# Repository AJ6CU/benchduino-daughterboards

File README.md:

# CPU Daughterboards Benchduino
 
www.hamradioworkbench.com has designed and sells a general purpose development
board for Microcontrollers. They have provided the designs for both the CPU
Daughterboards as wells as the addon Prototype board.

This repository contains additional CPU Daughterboards that I have designed.

Subdirectories include:
- Gerbers - this directory includes a zip file that you should be able to upload to
            your favorite Fab house.
- PCBDesign - Most of the designs are done with KiCad. A few of the earlier ones
            were done with Eagle. The subdirectory will indentify which tool was used. 
- Documentation - This directory contains a schematic (pdf format) and pinmapping between
            the Benchduino pins and the pins on the Microcontroller. Please note that
            some physical pins on the Microcontroller might be mapped to multiple 
            locations on the Benchduino. Please use this pinmapping document along
            with your favorite pinout diagram to understand which pins could cause
            conflicts.
- Examples - Generally I have provide a code example (typically derived from the
            original Hamvention code of the published on the hamradioworkbench site)

There is absolutely no warranty here. Use this at your own risk!

73
Mark Hatch
AJ6CU

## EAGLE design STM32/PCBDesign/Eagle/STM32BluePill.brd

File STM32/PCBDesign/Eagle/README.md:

# Eagle files for the STM32 "BluePill" Series MCU Daughterboard

This directory includes the Eagle files for a design of a Benchduino Daughterboard
(see https://www.hamradioworkbench.com ) for the STM32 "BluePill" series of MCU.

This folder includes:
- STM32BluePill.sch - schematic
- STM32BluePill.brd - board layout

It is possible that you will need the Eagle library for STM32. I found it with a little
googling.

In making this design, my philosophy was to try to make sure most Benchduino Pins were 
connected to appropriate pins if possible.

This means that some pins (e.g. SDA, and A4) are both active and map to the same pin 
on the STM32. So don't assume that because you have two pins, that they are separate. 
The STM32 pin guide is your friend to make sure you don't use the same pin twice
for a different purpose.

Feedback is appreciated!

73
Mark
AJ6CU

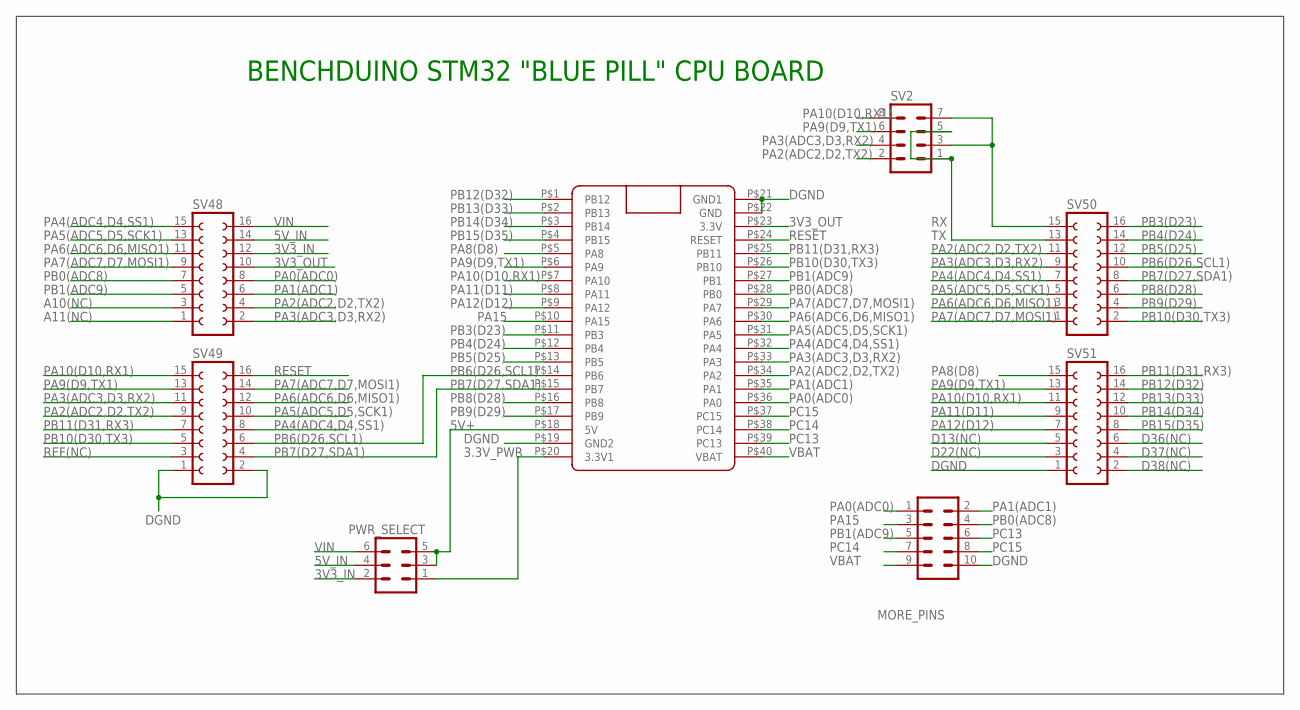
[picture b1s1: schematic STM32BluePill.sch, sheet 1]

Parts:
MORE_PINS: MA05-2
PWR_SELECT: MA03-2
SV2: MA04-2
SV48, SV49, SV50, SV51: FE08-2
U$1: BLUE_PILLADVANCED; BLUE_PILL_ADV

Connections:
3.3V_PWR: PWR_SELECT.1, U$1.P$20 (3.3V1)
3V3_IN: PWR_SELECT.2, SV48.12
3V3_OUT: SV48.10, U$1.P$23 (3.3V)
5V+: PWR_SELECT.3, PWR_SELECT.5, U$1.P$18 (5V)
5V_IN: PWR_SELECT.4, SV48.14
A10(NC): SV48.3
A11(NC): SV48.1
D13(NC): SV51.5
D22(NC): SV51.3
D36(NC): SV51.6
D37(NC): SV51.4
D38(NC): SV51.2
DGND: MORE_PINS.10, SV49.1, SV49.2, SV51.1, U$1.P$19 (GND2), U$1.P$21 (GND1), U$1.P$22 (GND)
PA0(ADC0): MORE_PINS.1, SV48.8, U$1.P$36 (PA0)
PA1(ADC1): MORE_PINS.2, SV48.6, U$1.P$35 (PA1)
PA2(ADC2,D2,TX2): SV2.2, SV48.4, SV49.9, SV50.11, U$1.P$34 (PA2)
PA3(ADC3,D3,RX2): SV2.4, SV48.2, SV49.11, SV50.9, U$1.P$33 (PA3)
PA4(ADC4,D4,SS1): SV48.15, SV49.8, SV50.7, U$1.P$32 (PA4)
PA5(ADC5,D5,SCK1): SV48.13, SV49.10, SV50.5, U$1.P$31 (PA5)
PA6(ADC6,D6,MISO1): SV48.11, SV49.12, SV50.3, U$1.P$30 (PA6)
PA7(ADC7,D7,MOSI1): SV48.9, SV49.14, SV50.1, U$1.P$29 (PA7)
PA8(D8): SV51.15, U$1.P$5 (PA8)
PA9(D9,TX1): SV2.6, SV49.13, SV51.13, U$1.P$6 (PA9)
PA10(D10,RX1): SV2.8, SV49.15, SV51.11, U$1.P$7 (PA10)
PA11(D11): SV51.9, U$1.P$8 (PA11)
PA12(D12): SV51.7, U$1.P$9 (PA12)
PA15: MORE_PINS.3, U$1.P$10 (PA15)
PB0(ADC8): MORE_PINS.4, SV48.7, U$1.P$28 (PB0)
PB1(ADC9): MORE_PINS.5, SV48.5, U$1.P$27 (PB1)
PB3(D23): SV50.16, U$1.P$11 (PB3)
PB4(D24): SV50.14, U$1.P$12 (PB4)
PB5(D25): SV50.12, U$1.P$13 (PB5)
PB6(D26,SCL1): SV49.6, SV50.10, U$1.P$14 (PB6)
PB7(D27,SDA1): SV49.4, SV50.8, U$1.P$15 (PB7)
PB8(D28): SV50.6, U$1.P$16 (PB8)
PB9(D29): SV50.4, U$1.P$17 (PB9)
PB10(D30,TX3): SV49.5, SV50.2, U$1.P$26 (PB10)
PB11(D31,RX3): SV49.7, SV51.16, U$1.P$25 (PB11)
PB12(D32): SV51.14, U$1.P$1 (PB12)
PB13(D33): SV51.12, U$1.P$2 (PB13)
PB14(D34): SV51.10, U$1.P$3 (PB14)
PB15(D35): SV51.8, U$1.P$4 (PB15)
PC13: MORE_PINS.6, U$1.P$39 (PC13)
PC14: MORE_PINS.7, U$1.P$38 (PC14)
PC15: MORE_PINS.8, U$1.P$37 (PC15)
REF(NC): SV49.3
RESET: SV49.16, U$1.P$24 (RESET)
RX: SV2.3, SV2.7, SV50.15
TX: SV2.1, SV2.5, SV50.13
VBAT: MORE_PINS.9, U$1.P$40 (VBAT)
VIN: PWR_SELECT.6, SV48.16

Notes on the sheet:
BENCHDUINO STM32 "BLUE PILL" CPU BOARD

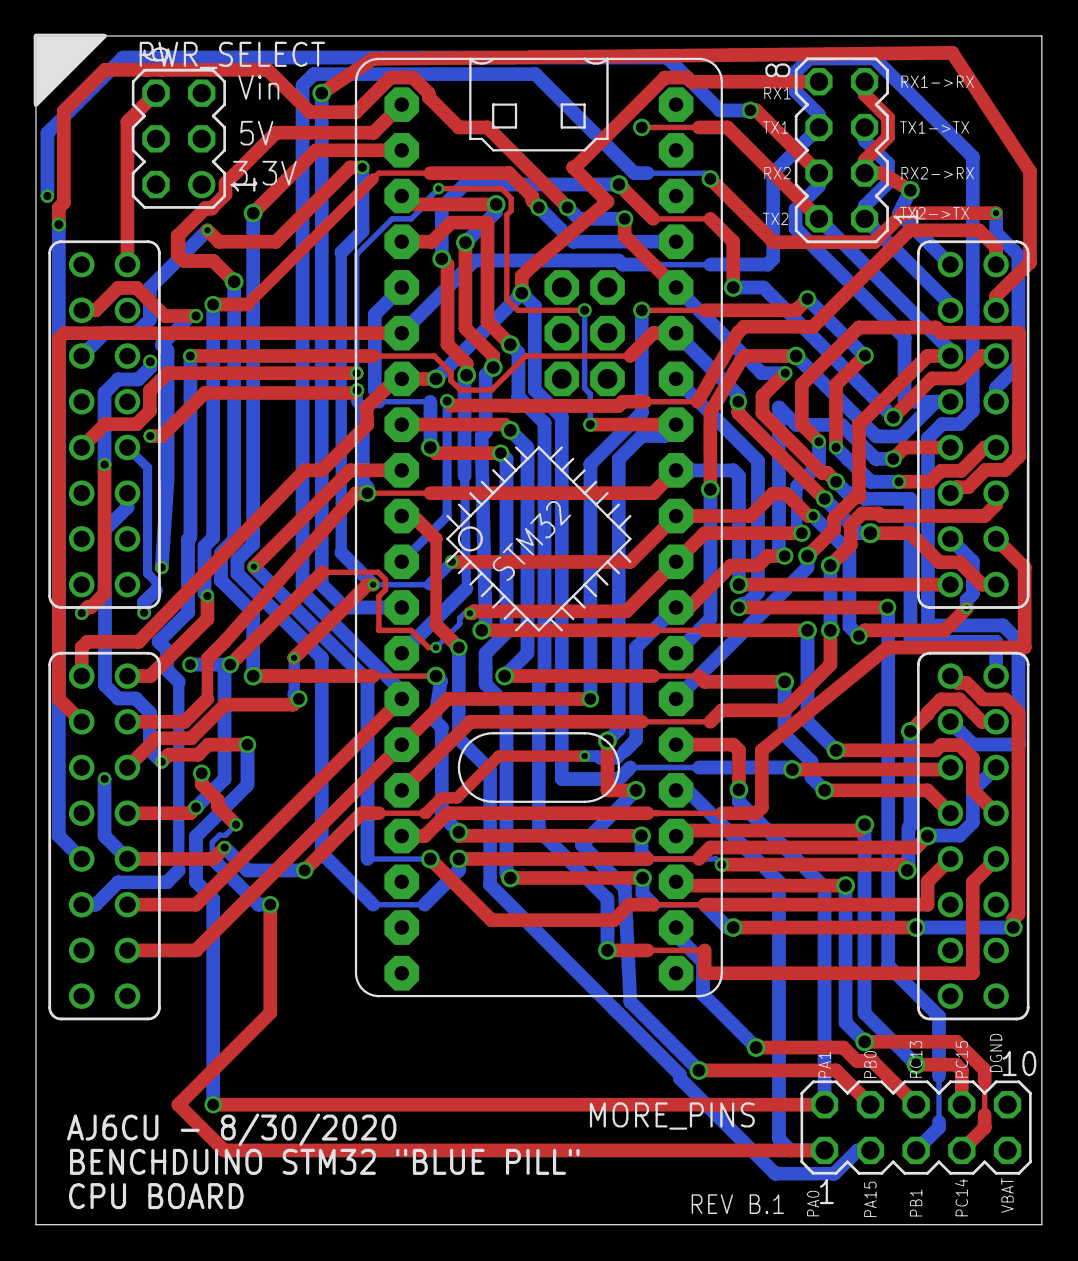
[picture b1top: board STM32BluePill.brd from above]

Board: 4 copper layers, 55.9 x 66.0 mm, 8 parts (0 on the bottom side), 43 nets.

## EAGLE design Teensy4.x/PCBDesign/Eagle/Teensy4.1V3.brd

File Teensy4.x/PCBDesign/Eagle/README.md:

# Eagle files for the Teensy 4.x Series MCU Daughterboard

This directory includes the Eagle files for a design of a Benchduino Daughterboard
(see https://www.hamradioworkbench.com ) for the Teensy 4.x series of MCU.

This has only been tested on the 4.1 version, and since the 4.0 is just a shortened
version of the 4.1 with the same pinout, it *should* work too. But it has not been tested.

This folder includes:
- Teensy4.1V3.sch - schematic
- Teensy4.1V3.brd - board layout

It is possible that you will need the Eagle library for Teensy. I found it

https://forum.pjrc.com/attachment.php?attachmentid=20116&d=1589570415

In making this design, my philosophy was to try to make sure most Benchduino Pins were 
connected to appropriate pins if possible.

This means that some pins (e.g. SDA, and A4) are both active and map to the same pin 
on the Teensy. So don't assume that because you have two pins, that they are separate. 
The Teensy pin guide is your friend to make sure you don't use the same pin twice
for a different purpose.

Feedback is appreciated!

73
Mark
AJ6CU

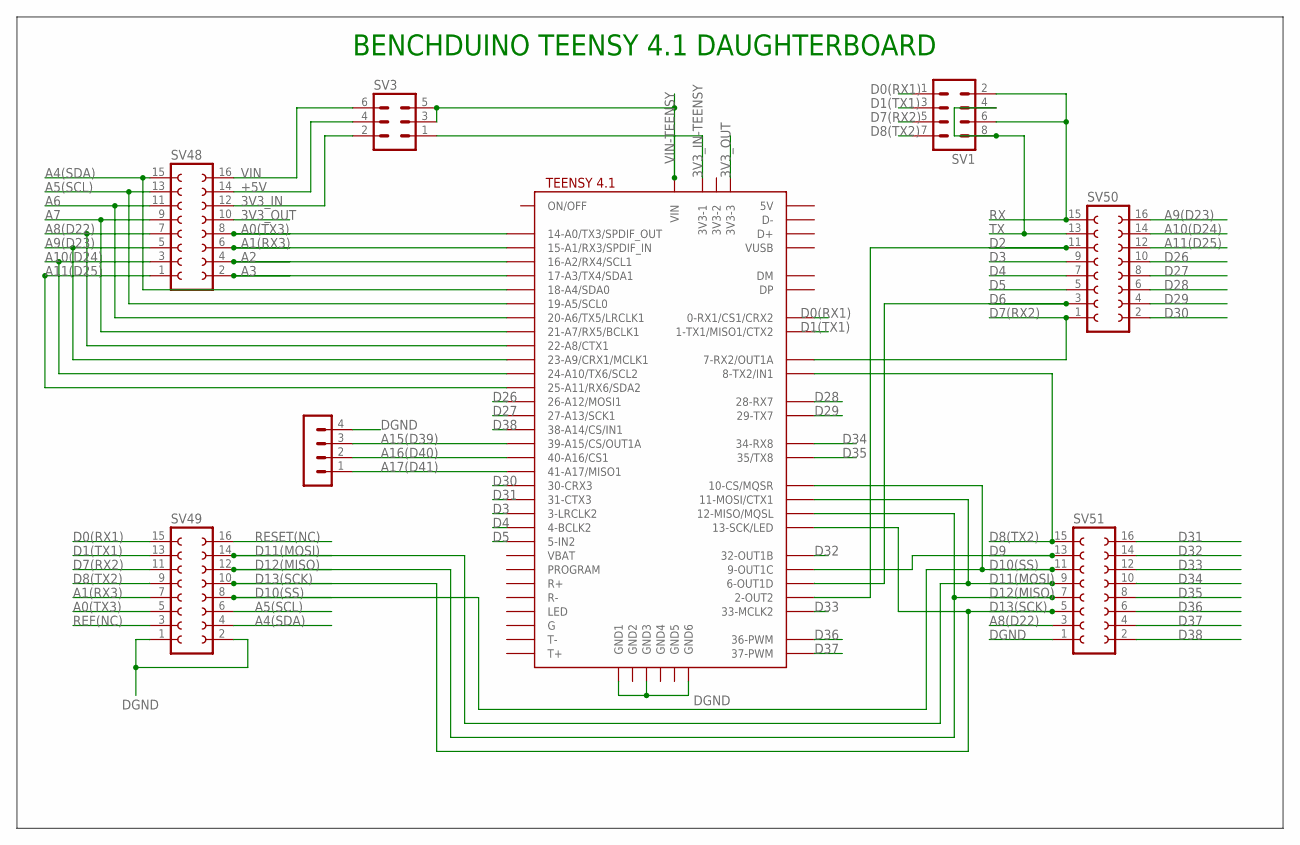
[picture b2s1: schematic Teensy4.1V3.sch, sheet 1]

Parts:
SV1: MA04-2
SV3: MA03-2
SV4: MA04-1
SV48, SV49, SV50, SV51: FE08-2
U$1: TEENSY41

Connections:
3V3_IN: SV3.2, SV48.12
3V3_IN-TEENSY: SV3.1, U$1.3V3-1
3V3_OUT: SV48.10, U$1.3V3-3
+5V: SV3.4, SV48.14
A0(TX3): SV48.8, SV49.5, U$1.14-A0/TX3/SPDIF_OUT
A1(RX3): SV48.6, SV49.7, U$1.15-A1/RX3/SPDIF_IN
A2: SV48.4, U$1.16-A2/RX4/SCL1
A3: SV48.2, U$1.17-A3/TX4/SDA1
A4(SDA): SV48.15, SV49.4, U$1.18-A4/SDA0
A5(SCL): SV48.13, SV49.6, U$1.19-A5/SCL0
A6: SV48.11, U$1.20-A6/TX5/LRCLK1
A7: SV48.9, U$1.21-A7/RX5/BCLK1
A8(D22): SV48.7, SV51.3, U$1.22-A8/CTX1
A9(D23): SV48.5, SV50.16, U$1.23-A9/CRX1/MCLK1
A10(D24): SV48.3, SV50.14, U$1.24-A10/TX6/SCL2
A11(D25): SV48.1, SV50.12, U$1.25-A11/RX6/SDA2
A15(D39): SV4.3, U$1.39-A15/CS/OUT1A
A16(D40): SV4.2, U$1.40-A16/CS1
A17(D41): SV4.1, U$1.41-A17/MISO1
D0(RX1): SV1.1, SV49.15, U$1.0-RX1/CS1/CRX2
D1(TX1): SV1.3, SV49.13, U$1.1-TX1/MISO1/CTX2
D2: SV50.11, U$1.2-OUT2
D3: SV50.9, U$1.3-LRCLK2
D4: SV50.7, U$1.4-BCLK2
D5: SV50.5, U$1.5-IN2
D6: SV50.3, U$1.6-OUT1D
D7(RX2): SV1.5, SV49.11, SV50.1, U$1.7-RX2/OUT1A
D8(TX2): SV1.7, SV49.9, SV51.15, U$1.8-TX2/IN2 (8-TX2/IN1)
D9: SV51.13, U$1.9-OUT1C
D10(SS): SV49.8, SV51.11, U$1.10-CS\MQSR (10-CS/MQSR)
D11(MOSI): SV49.14, SV51.9, U$1.11-MOSI/CTX1
D12(MISO): SV49.12, SV51.7, U$1.12-MISO/MQSL
D13(SCK): SV49.10, SV51.5, U$1.13-SCK/LED
D26: SV50.10, U$1.26-A12/MOSI1
D27: SV50.8, U$1.27-A13/SCK1
D28: SV50.6, U$1.28-RX7
D29: SV50.4, U$1.29-TX7
D30: SV50.2, U$1.30-CRX3
D31: SV51.16, U$1.31-CTX3
D32: SV51.14, U$1.32-OUT1B
D33: SV51.12, U$1.33-MCLK2
D34: SV51.10, U$1.34-RX8
D35: SV51.8, U$1.35-TX8 (35/TX8)
D36: SV51.6, U$1.36-PWM
D37: SV51.4, U$1.37-PWM
D38: SV51.2, U$1.38-A14/CS/IN1
DGND: SV4.4, SV49.1, SV49.2, SV51.1, U$1.GND1, U$1.GND3, U$1.GND6
REF(NC): SV49.3
RESET(NC): SV49.16
RX: SV1.2, SV1.6, SV50.15
TX: SV1.4, SV1.8, SV50.13
VIN: SV3.6, SV48.16
VIN-TEENSY: SV3.3, SV3.5, U$1.VIN

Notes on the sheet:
BENCHDUINO TEENSY 4.1 DAUGHTERBOARD

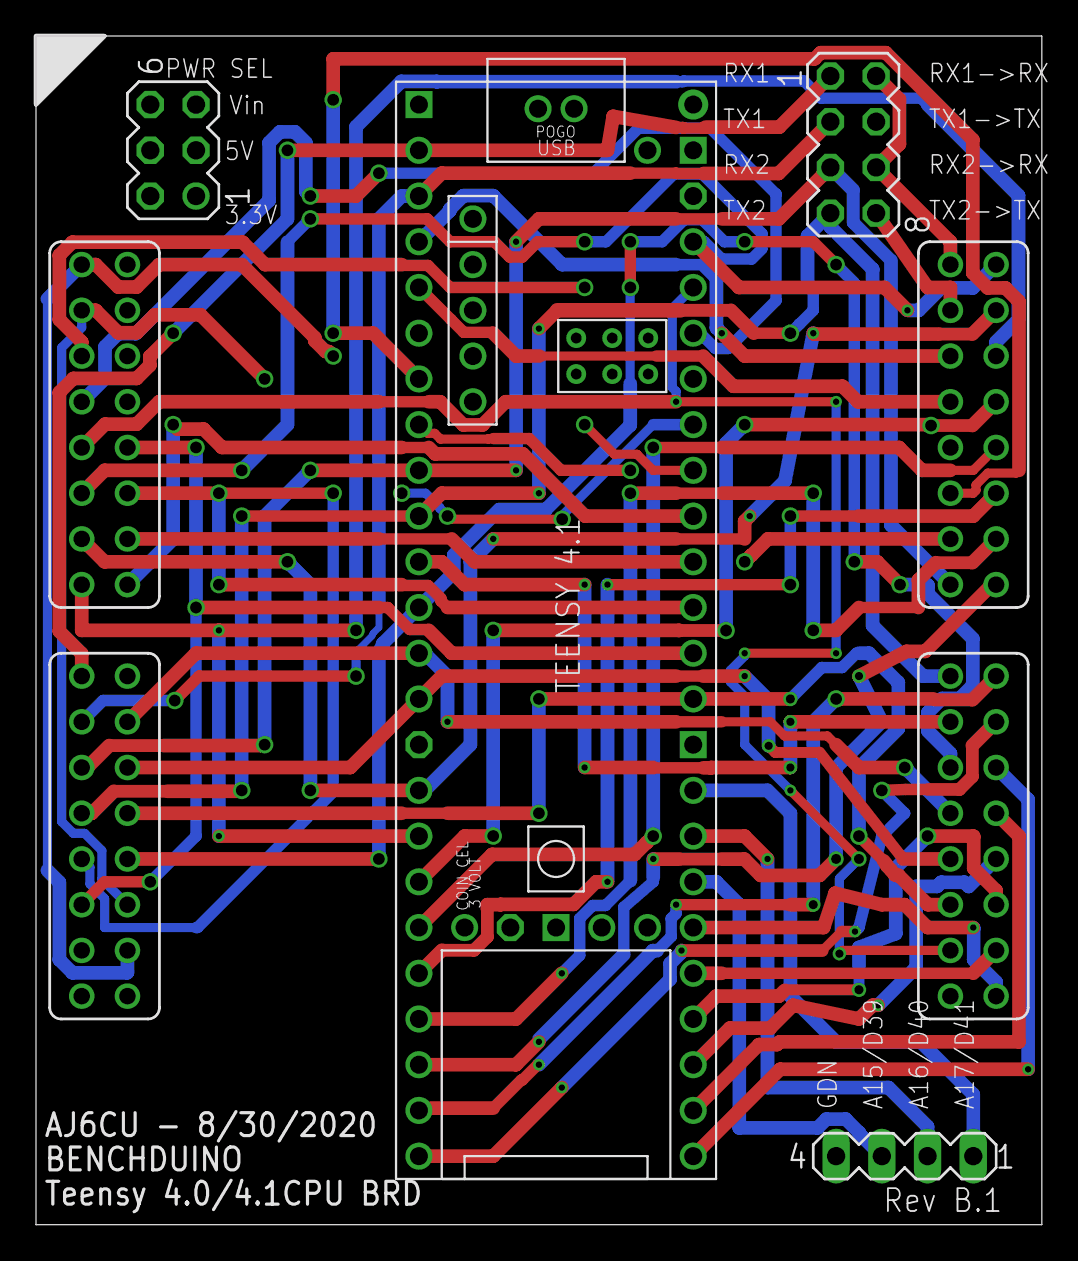
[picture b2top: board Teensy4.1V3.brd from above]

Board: 4 copper layers, 55.9 x 66.0 mm, 8 parts (0 on the bottom side), 51 nets.

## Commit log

2020-08-25 testing
    test
2020-08-25 deletion of test files
2020-08-25 Get rid of the .DSTORE
2020-08-25 added STM32 Folder
2020-08-25 changed director name
2020-08-25 Population of folders for each daughterboard
2020-08-25 Removed ignoring of compressed files
2020-08-25 Eagle files for Teensy 4.x added
2020-08-25 Format change
2020-08-25 Formating change
2020-08-25 adding schematic and photo
2020-08-25 Renamed photo
2020-08-30 Updated Teensy to correct power error
2020-08-31 Added STM32
2020-08-31 refine readme, add nano and xiao processors
2020-08-31 fix kicad spelling
2020-08-31 add back in pcb
2020-08-31 deleted pcb for rename
2020-08-31 add back in pcbdesign
2020-08-31 file structued pushed for esp32
2020-08-31 Final commit before production
2020-08-31 added board models/photos
2020-09-13 Updated readme's to reflect fabrication success
